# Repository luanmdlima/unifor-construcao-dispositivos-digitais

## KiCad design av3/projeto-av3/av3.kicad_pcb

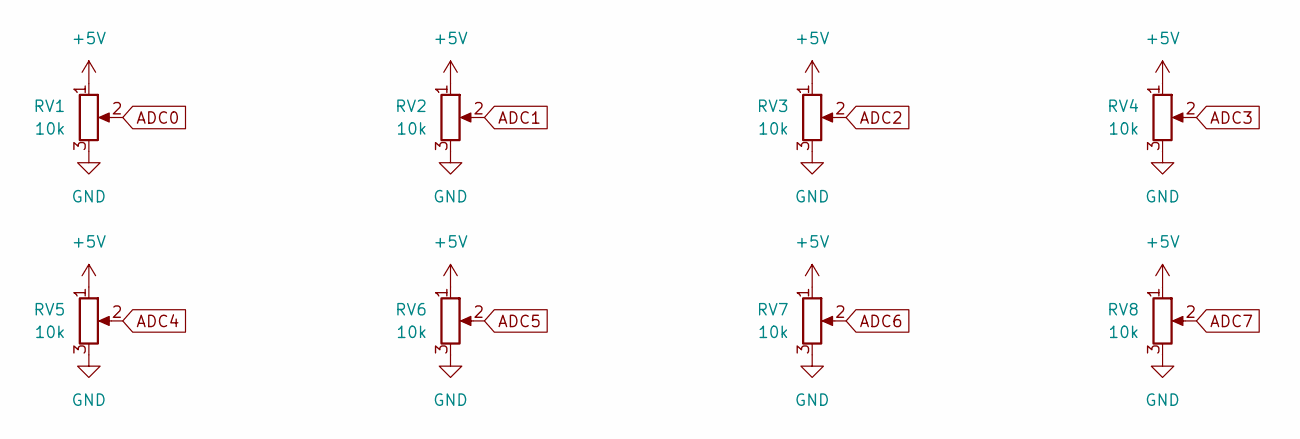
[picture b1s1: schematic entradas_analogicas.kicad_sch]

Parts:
RV1, RV2, RV3, RV4, RV5, RV6, RV7, RV8: 10k; Potentiometer_Bourns_3296W_Vertical

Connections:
+5V: RV1.1, RV2.1, RV3.1, RV4.1, RV5.1, RV6.1, RV7.1, RV8.1; also elsewhere on the board
ADC0: RV1.2; also elsewhere on the board
ADC1: RV2.2; also elsewhere on the board
ADC2: RV3.2; also elsewhere on the board
ADC3: RV4.2; also elsewhere on the board
ADC4: RV5.2; also elsewhere on the board
ADC5: RV6.2; also elsewhere on the board
ADC6: RV7.2; also elsewhere on the board
ADC7: RV8.2; also elsewhere on the board
GND: RV1.3, RV2.3, RV3.3, RV4.3, RV5.3, RV6.3, RV7.3, RV8.3; also elsewhere on the board

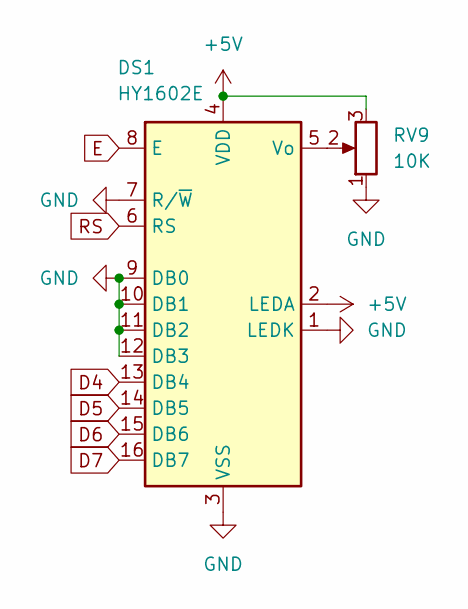
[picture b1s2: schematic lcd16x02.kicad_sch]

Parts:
DS1: HY1602E
RV9: 10K; Potentiometer_Bourns_3296W_Vertical

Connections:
+5V: DS1.2 (LEDA), DS1.4 (VDD), RV9.3; also elsewhere on the board
D4: DS1.13 (DB4); also elsewhere on the board
D5: DS1.14 (DB5); also elsewhere on the board
D6: DS1.15 (DB6); also elsewhere on the board
D7: DS1.16 (DB7); also elsewhere on the board
E: DS1.8 (E); also elsewhere on the board
GND: DS1.1 (LEDK), DS1.3 (VSS), DS1.7 (R/~W), DS1.9 (DB0), DS1.10 (DB1), DS1.11 (DB2), DS1.12 (DB3), RV9.1; also elsewhere on the board
unnamed: DS1.5 (Vo), RV9.2
RS: DS1.6 (RS); also elsewhere on the board

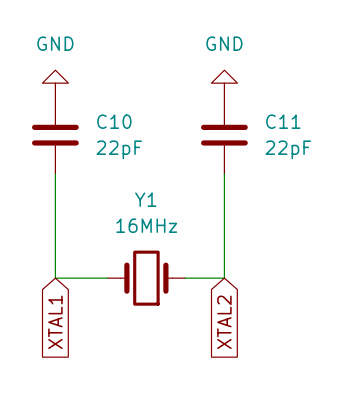
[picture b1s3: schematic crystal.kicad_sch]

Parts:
C10, C11: 22pF; C_1206_3216Metric
Y1: 16MHz; Crystal_SMD_HC49-SD

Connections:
GND: C10.2, C11.2; also elsewhere on the board
XTAL1: C10.1, Y1.2; also elsewhere on the board
XTAL2: C11.1, Y1.1; also elsewhere on the board

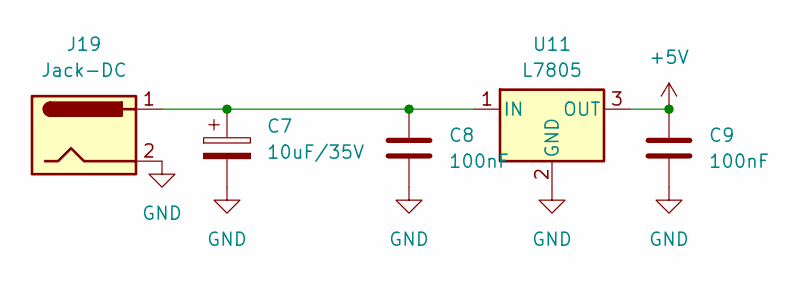
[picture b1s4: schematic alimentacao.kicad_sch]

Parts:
C7: 10uF/35V; CP_Elec_5x5.7
C8, C9: 100nF; C_1206_3216Metric
J19: Jack-DC; BarrelJack_Horizontal
U11: L7805; TO-220-3_Horizontal_TabDown

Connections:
+5V: C9.1, U11.3 (OUT); also elsewhere on the board
GND: C7.2, C8.2, C9.2, J19.2, U11.2 (GND); also elsewhere on the board
unnamed: C7.1, C8.1, J19.1, U11.1 (IN)

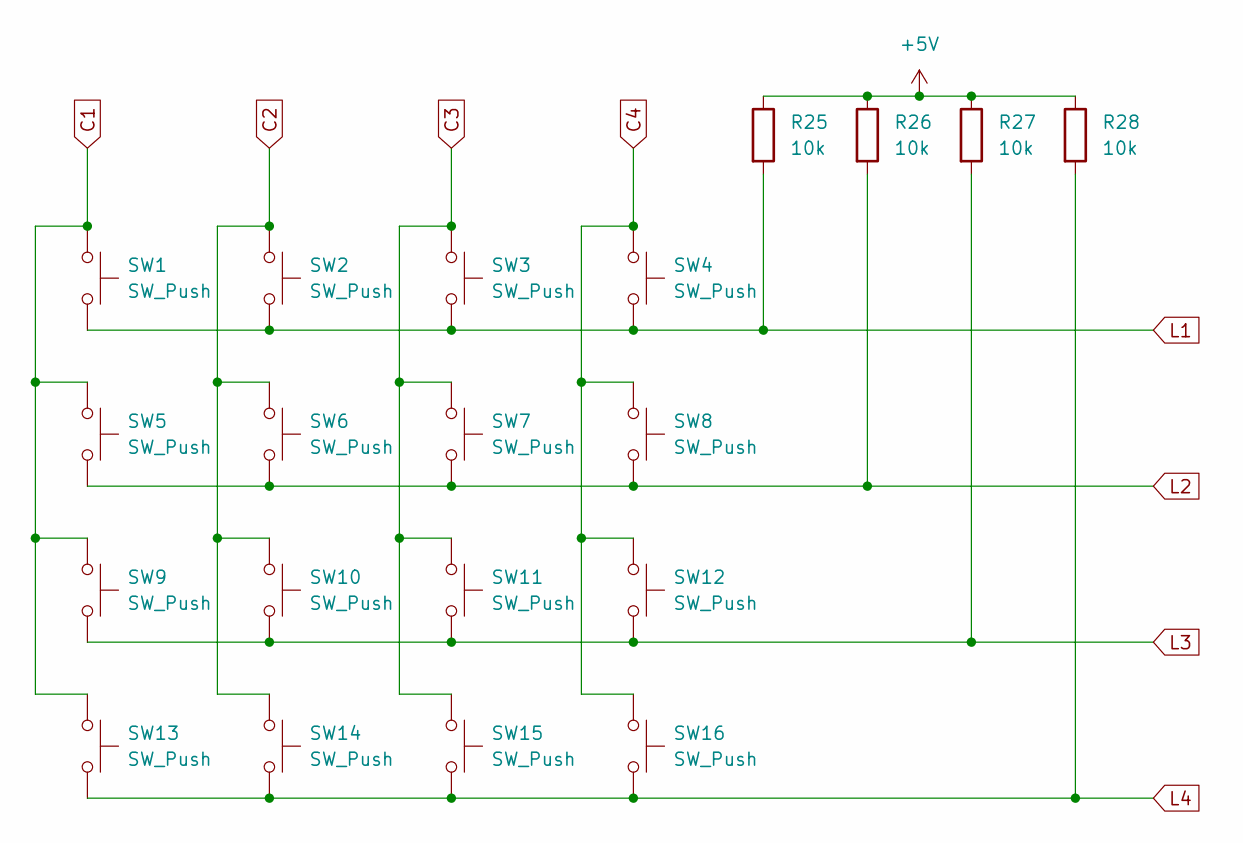
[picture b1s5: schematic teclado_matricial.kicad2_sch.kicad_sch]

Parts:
R25, R26, R27, R28: 10k; R_1206_3216Metric_Pad1.30x1.75mm_HandSolder
SW1, SW2, SW3, SW4, SW5, SW6, SW7, SW8, SW9, SW10, SW11, SW12, SW13, SW14, SW15, SW16: SW_Push; SW_PUSH_6mm_H4.3mm

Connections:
+5V: R25.1, R26.1, R27.1, R28.1; also elsewhere on the board
C1: SW1.1, SW5.1, SW9.1, SW13.1; also elsewhere on the board
C2: SW2.1, SW6.1, SW10.1, SW14.1; also elsewhere on the board
C3: SW3.1, SW7.1, SW11.1, SW15.1; also elsewhere on the board
C4: SW4.1, SW8.1, SW12.1, SW16.1; also elsewhere on the board
L1: R25.2, SW1.2, SW2.2, SW3.2, SW4.2; also elsewhere on the board
L2: R26.2, SW5.2, SW6.2, SW7.2, SW8.2; also elsewhere on the board
L3: R27.2, SW9.2, SW10.2, SW11.2, SW12.2; also elsewhere on the board
L4: R28.2, SW13.2, SW14.2, SW15.2, SW16.2; also elsewhere on the board

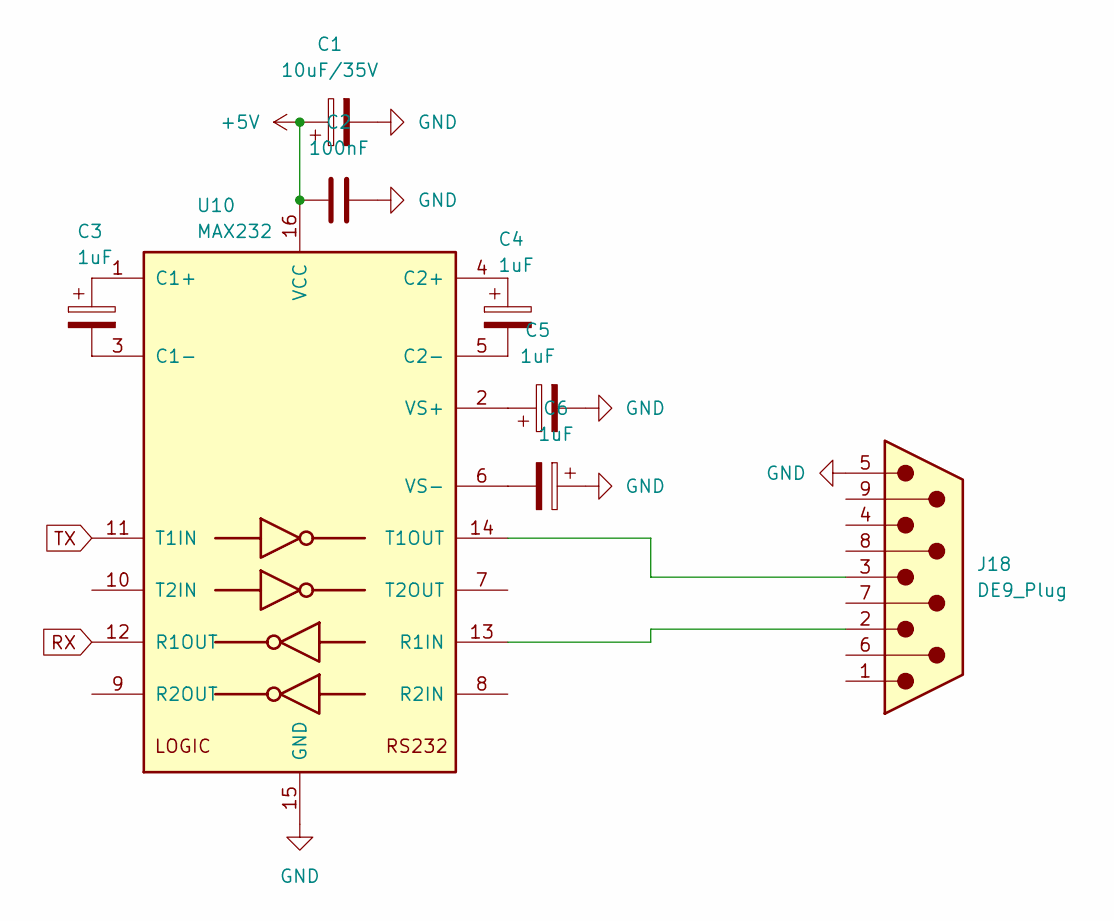
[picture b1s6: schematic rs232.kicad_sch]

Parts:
C1: 10uF/35V; CP_Elec_5x5.7
C2: 100nF; C_1206_3216Metric
C3, C4, C5, C6: 1uF; CP_Elec_3x5.3
J18: DE9_Plug; DSUB-9_Female_Horizontal_P2.77x2.84mm_EdgePinOffset4.94mm_H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
U10: MAX232; SOIC-16_4.55x10.3mm_P1.27mm

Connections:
+5V: C1.1, C2.1, U10.16 (VCC); also elsewhere on the board
GND: C1.2, C2.2, C5.2, C6.1, J18.5, U10.15 (GND); also elsewhere on the board
unnamed: C3.1, U10.1 (C1+)
unnamed: C3.2, U10.3 (C1-)
unnamed: C4.1, U10.4 (C2+)
unnamed: C4.2, U10.5 (C2-)
unnamed: J18.2, U10.13 (R1IN)
unnamed: J18.3, U10.14 (T1OUT)
unnamed: C5.1, U10.2 (VS+)
unnamed: C6.2, U10.6 (VS-)
RX: U10.12 (R1OUT); also elsewhere on the board
TX: U10.11 (T1IN); also elsewhere on the board

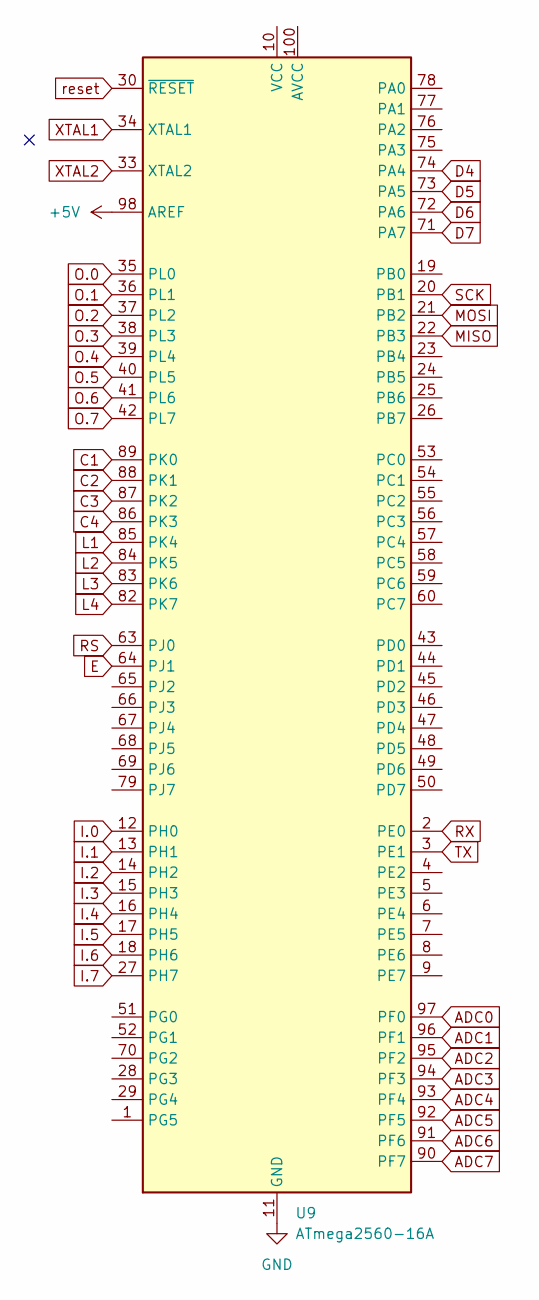
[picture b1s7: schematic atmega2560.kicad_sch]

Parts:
U9: ATmega2560-16A; TQFP-100_14x14mm_P0.5mm

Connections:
+5V: U9.98 (AREF); also elsewhere on the board
ADC0: U9.97 (PF0); also elsewhere on the board
ADC1: U9.96 (PF1); also elsewhere on the board
ADC2: U9.95 (PF2); also elsewhere on the board
ADC3: U9.94 (PF3); also elsewhere on the board
ADC4: U9.93 (PF4); also elsewhere on the board
ADC5: U9.92 (PF5); also elsewhere on the board
ADC6: U9.91 (PF6); also elsewhere on the board
ADC7: U9.90 (PF7); also elsewhere on the board
C1: U9.89 (PK0); also elsewhere on the board
C2: U9.88 (PK1); also elsewhere on the board
C3: U9.87 (PK2); also elsewhere on the board
C4: U9.86 (PK3); also elsewhere on the board
D4: U9.74 (PA4); also elsewhere on the board
D5: U9.73 (PA5); also elsewhere on the board
D6: U9.72 (PA6); also elsewhere on the board
D7: U9.71 (PA7); also elsewhere on the board
E: U9.64 (PJ1); also elsewhere on the board
GND: U9.11 (GND), U9.32 (GND), U9.62 (GND), U9.81 (GND), U9.99 (GND); also elsewhere on the board
I.0: U9.12 (PH0); also elsewhere on the board
I.1: U9.13 (PH1); also elsewhere on the board
I.2: U9.14 (PH2); also elsewhere on the board
I.3: U9.15 (PH3); also elsewhere on the board
I.4: U9.16 (PH4); also elsewhere on the board
I.5: U9.17 (PH5); also elsewhere on the board
I.6: U9.18 (PH6); also elsewhere on the board
I.7: U9.27 (PH7); also elsewhere on the board
L1: U9.85 (PK4); also elsewhere on the board
L2: U9.84 (PK5); also elsewhere on the board
L3: U9.83 (PK6); also elsewhere on the board
L4: U9.82 (PK7); also elsewhere on the board
MISO: U9.22 (PB3); also elsewhere on the board
MOSI: U9.21 (PB2); also elsewhere on the board
unnamed: U9.10 (VCC), U9.31 (VCC), U9.61 (VCC), U9.80 (VCC)
O.0: U9.35 (PL0); also elsewhere on the board
O.1: U9.36 (PL1); also elsewhere on the board
O.2: U9.37 (PL2); also elsewhere on the board
O.3: U9.38 (PL3); also elsewhere on the board
O.4: U9.39 (PL4); also elsewhere on the board
O.5: U9.40 (PL5); also elsewhere on the board
O.6: U9.41 (PL6); also elsewhere on the board
O.7: U9.42 (PL7); also elsewhere on the board
RS: U9.63 (PJ0); also elsewhere on the board
RX: U9.2 (PE0); also elsewhere on the board
SCK: U9.20 (PB1); also elsewhere on the board
TX: U9.3 (PE1); also elsewhere on the board
XTAL1: U9.34 (XTAL1); also elsewhere on the board
XTAL2: U9.33 (XTAL2); also elsewhere on the board
reset: U9.30 (~RESET); also elsewhere on the board

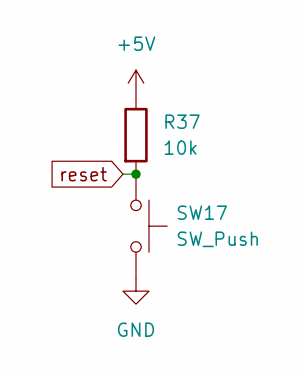
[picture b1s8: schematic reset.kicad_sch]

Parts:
R37: 10k; R_1206_3216Metric_Pad1.30x1.75mm_HandSolder
SW17: SW_Push; SW_PUSH_6mm_H4.3mm

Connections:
+5V: R37.1; also elsewhere on the board
GND: SW17.2; also elsewhere on the board
reset: R37.2, SW17.1; also elsewhere on the board

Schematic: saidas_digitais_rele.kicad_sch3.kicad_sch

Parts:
D17, D18, D19, D20, D21, D22, D23, D24: 1N4148; D_DO-35_SOD27_P7.62mm_Horizontal
J9, J10, J11, J12, J13, J14, J15, J16: Conn_01x03; TerminalBlock_Phoenix_MKDS-1,5-3-5.08_1x03_P5.08mm_Horizont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
K1, K2, K3, K4, K5, K6, K7, K8: SANYOU_SRD_Form_C; Relay_SPDT_SANYOU_SRD_Series_Form_C
Q1, Q2, Q3, Q4, Q5, Q6, Q7, Q8: BC548; TO-92_Inline
R29, R30, R31, R32, R33, R34, R35, R36: 1k; R_Axial_DIN0204_L3.6mm_D1.6mm_P5.08mm_Horizontal

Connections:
+5V: D17.1 (K), D18.1 (K), D19.1 (K), D20.1 (K), D21.1 (K), D22.1 (K), D23.1 (K), D24.1 (K), K1.2, K2.2, K3.2, K4.2, K5.2, K6.2, K7.2, K8.2; also elsewhere on the board
GND: Q1.3 (E), Q2.3 (E), Q3.3 (E), Q4.3 (E), Q5.3 (E), Q6.3 (E), Q7.3 (E), Q8.3 (E); also elsewhere on the board
unnamed: D17.2 (A), K1.5, Q1.1 (C)
unnamed: D18.2 (A), K2.5, Q2.1 (C)
unnamed: D19.2 (A), K3.5, Q3.1 (C)
unnamed: D20.2 (A), K4.5, Q4.1 (C)
unnamed: D21.2 (A), K5.5, Q5.1 (C)
unnamed: D22.2 (A), K6.5, Q6.1 (C)
unnamed: D23.2 (A), K7.5, Q7.1 (C)
unnamed: D24.2 (A), K8.5, Q8.1 (C)
unnamed: J9.1, K1.3
unnamed: J9.2, K1.1
unnamed: J9.3, K1.4
unnamed: J10.1, K2.3
unnamed: J10.2, K2.1
unnamed: J10.3, K2.4
unnamed: J11.1, K3.3
unnamed: J11.2, K3.1
unnamed: J11.3, K3.4
unnamed: J12.1, K4.3
unnamed: J12.2, K4.1
unnamed: J12.3, K4.4
unnamed: J13.1, K5.3
unnamed: J13.2, K5.1
unnamed: J13.3, K5.4
unnamed: J14.1, K6.3
unnamed: J14.2, K6.1
unnamed: J14.3, K6.4
unnamed: J15.1, K7.3
unnamed: J15.2, K7.1
unnamed: J15.3, K7.4
unnamed: J16.1, K8.3
unnamed: J16.2, K8.1
unnamed: J16.3, K8.4
unnamed: Q1.2 (B), R29.2
unnamed: Q2.2 (B), R30.2
unnamed: Q3.2 (B), R31.2
unnamed: Q4.2 (B), R32.2
unnamed: Q5.2 (B), R33.2
unnamed: Q6.2 (B), R34.2
unnamed: Q7.2 (B), R35.2
unnamed: Q8.2 (B), R36.2
O.0: R29.1; also elsewhere on the board
O.1: R30.1; also elsewhere on the board
O.2: R31.1; also elsewhere on the board
O.3: R32.1; also elsewhere on the board
O.4: R33.1; also elsewhere on the board
O.5: R34.1; also elsewhere on the board
O.6: R35.1; also elsewhere on the board
O.7: R36.1; also elsewhere on the board

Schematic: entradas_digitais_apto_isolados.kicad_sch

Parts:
D1, D2, D3, D4, D9, D10, D12, D13: 1N4148; D_DO-35_SOD27_P7.62mm_Horizontal
D5, D6, D7, D8, D11, D14, D15, D16: LED; LED_1206_3216Metric
J1, J2, J3, J4, J5, J6, J7, J8: Conn_01x02; TerminalBlock_Phoenix_MKDS-1,5-2_1x02_P5.00mm_Horizontal
R1, R2, R3, R4, R5, R6, R7, R8, R13, R14, R15, R17, R18, R19, R20, R22: 10k; R_1206_3216Metric_Pad1.30x1.75mm_HandSolder
R9, R10, R11, R12, R16, R21, R23, R24: 1k; R_1206_3216Metric_Pad1.30x1.75mm_HandSolder
U1, U2, U3, U4, U5, U6, U7, U8: 4N25; DIP-6_W7.62mm_SMDSocket_SmallPads

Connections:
+5V: D1.1 (K), D2.1 (K), D3.1 (K), D4.1 (K), D9.1 (K), D10.1 (K), D12.1 (K), D13.1 (K), R5.2, R6.2, R7.2, R8.2, R14.2, R18.2, R20.2, R22.2; also elsewhere on the board
GND: U1.4, U2.4, U3.4, U4.4, U5.4, U6.4, U7.4, U8.4; also elsewhere on the board
I.0: R5.1, U1.5; also elsewhere on the board
I.1: R6.1, U2.5; also elsewhere on the board
I.2: R7.1, U3.5; also elsewhere on the board
I.3: R8.1, U4.5; also elsewhere on the board
I.4: R14.1, U5.5; also elsewhere on the board
I.5: R18.1, U6.5; also elsewhere on the board
I.6: R20.1, U7.5; also elsewhere on the board
I.7: R22.1, U8.5; also elsewhere on the board
unnamed: D1.2 (A), U1.6
unnamed: D2.2 (A), U2.6
unnamed: D3.2 (A), U3.6
unnamed: D4.2 (A), U4.6
unnamed: D5.2 (A), R9.2
unnamed: D5.1 (K), J1.2, U1.2
unnamed: D6.2 (A), R10.2
unnamed: D6.1 (K), J2.2, U2.2
unnamed: D7.2 (A), R11.2
unnamed: D7.1 (K), J3.2, U3.2
unnamed: D8.2 (A), R12.2
unnamed: D8.1 (K), J4.2, U4.2
unnamed: D9.2 (A), U5.6
unnamed: D10.2 (A), U6.6
unnamed: D11.2 (A), R16.2
unnamed: D11.1 (K), J5.2, U5.2
unnamed: D12.2 (A), U7.6
unnamed: D13.2 (A), U8.6
unnamed: D14.2 (A), R21.2
unnamed: D14.1 (K), J6.2, U6.2
unnamed: D15.2 (A), R23.2
unnamed: D15.1 (K), J7.2, U7.2
unnamed: D16.2 (A), R24.2
unnamed: D16.1 (K), J8.2, U8.2
unnamed: J1.1, R1.1, R9.1
unnamed: J2.1, R2.1, R10.1
unnamed: J3.1, R3.1, R11.1
unnamed: J4.1, R4.1, R12.1
unnamed: J5.1, R13.1, R16.1
unnamed: J6.1, R15.1, R21.1
unnamed: J7.1, R17.1, R23.1
unnamed: J8.1, R19.1, R24.1
unnamed: R1.2, U1.1
unnamed: R2.2, U2.1
unnamed: R3.2, U3.1
unnamed: R4.2, U4.1
unnamed: R13.2, U5.1
unnamed: R15.2, U6.1
unnamed: R17.2, U7.1
unnamed: R19.2, U8.1

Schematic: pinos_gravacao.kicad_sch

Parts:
J17: Conn_02x03_Odd_Even; PinHeader_2x03_P2.54mm_Vertical_SMD

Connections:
+5V: J17.2; also elsewhere on the board
GND: J17.6; also elsewhere on the board
MISO: J17.1; also elsewhere on the board
MOSI: J17.4; also elsewhere on the board
SCK: J17.3; also elsewhere on the board
reset: J17.5; also elsewhere on the board

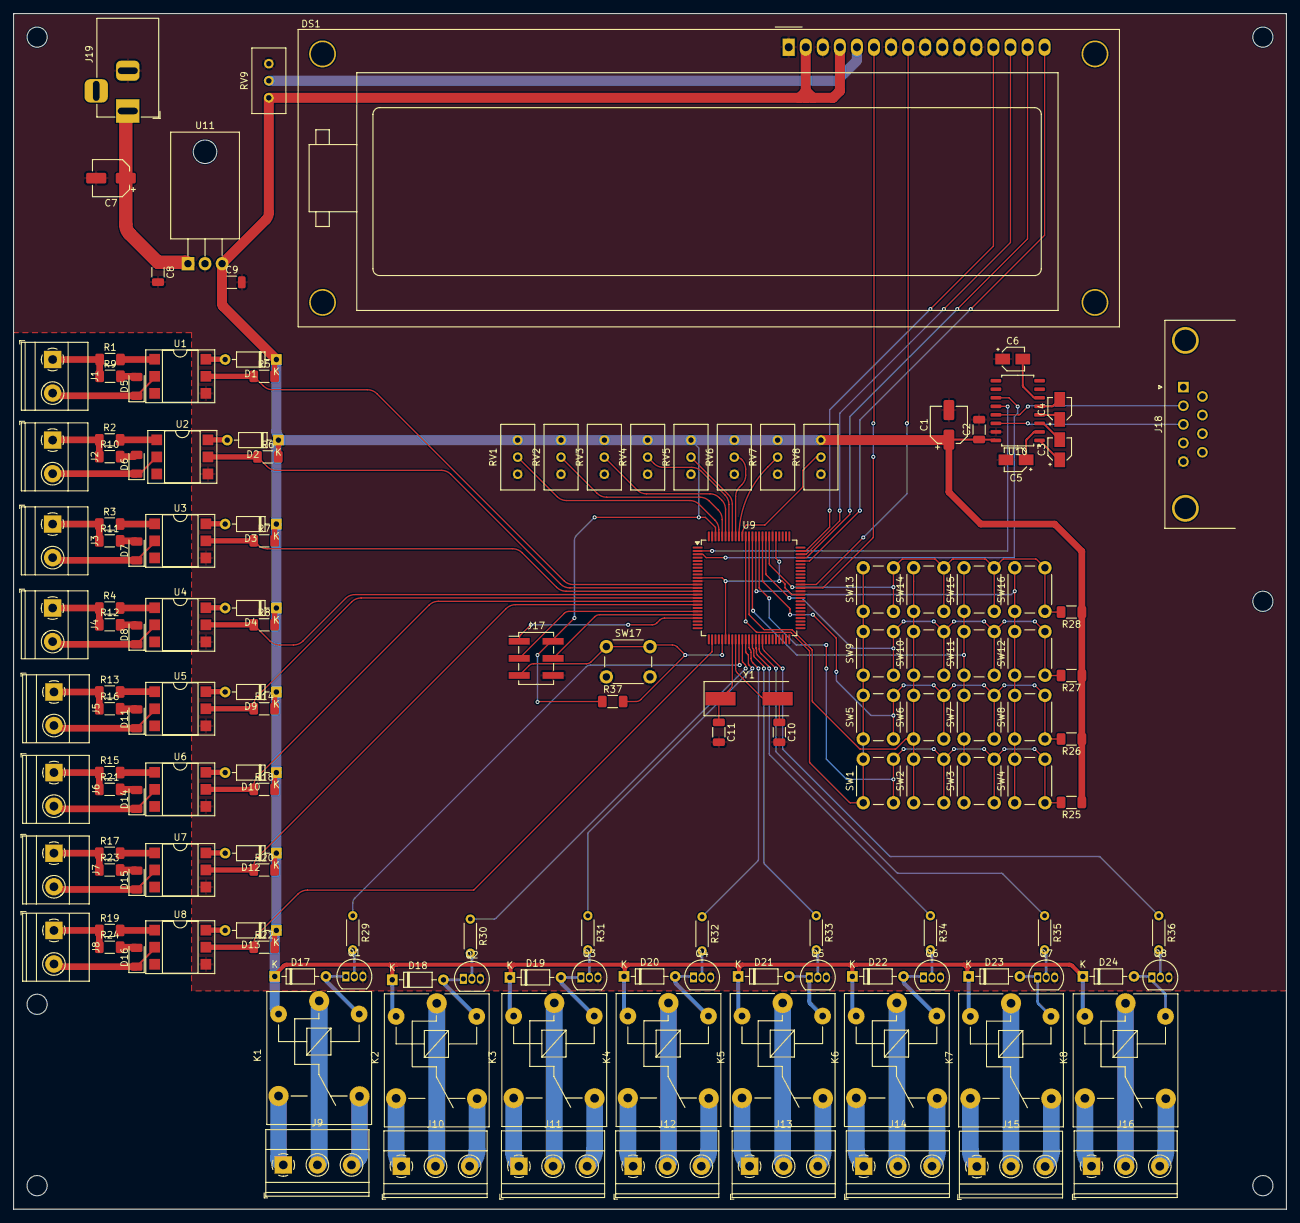
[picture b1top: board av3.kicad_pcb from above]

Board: 2 copper layers, 189.5 x 178.0 mm, 146 parts (0 on the bottom side), 139 nets.

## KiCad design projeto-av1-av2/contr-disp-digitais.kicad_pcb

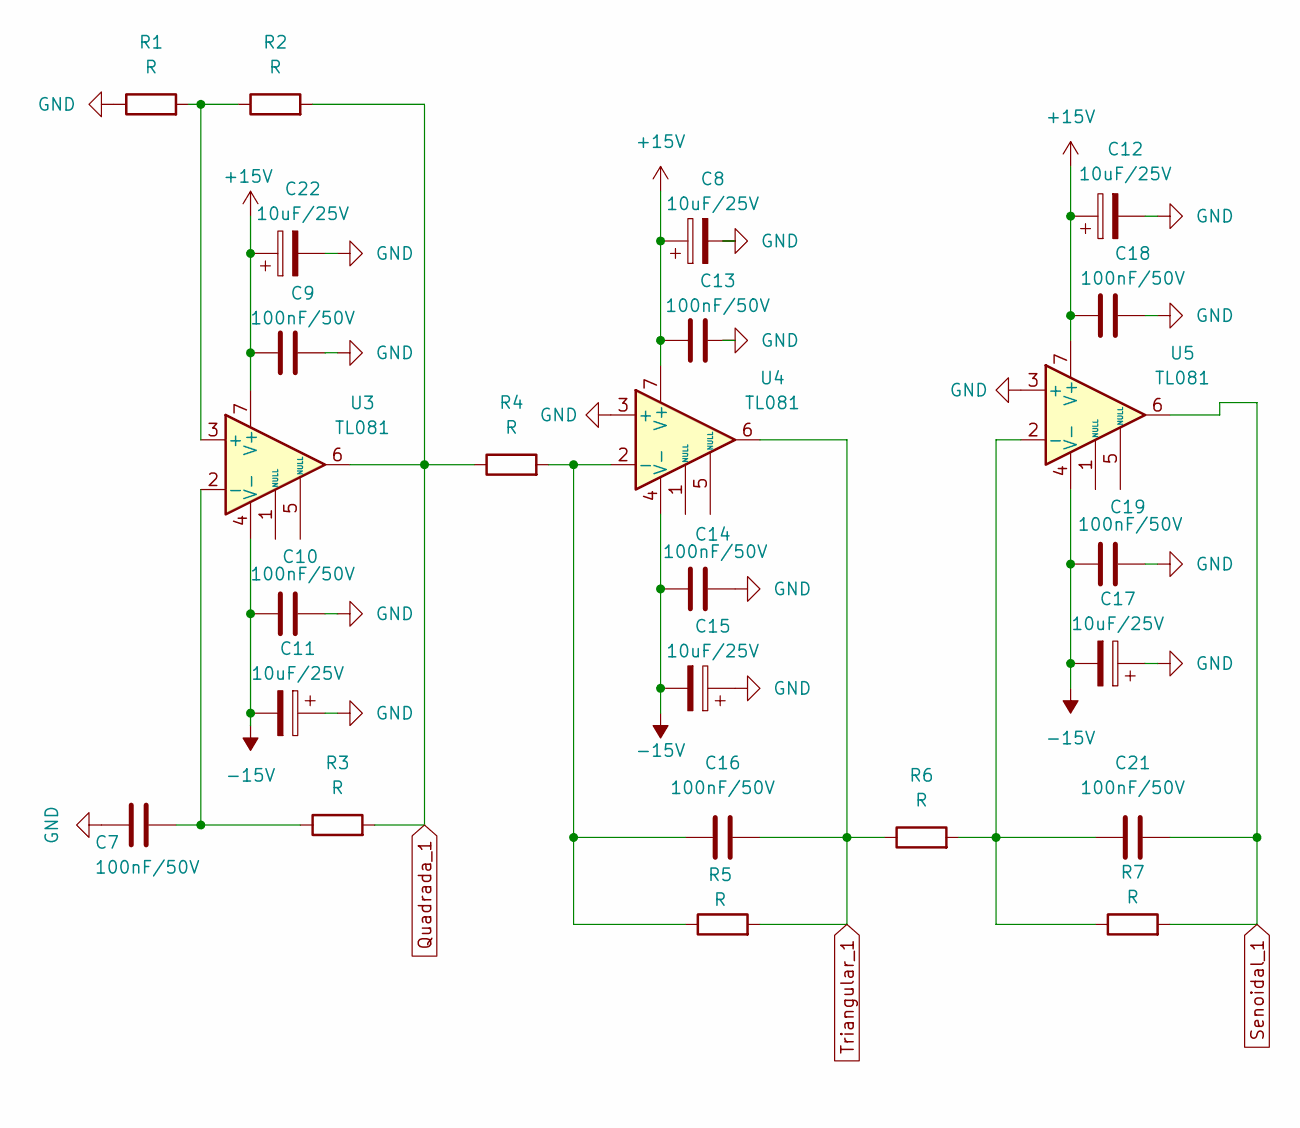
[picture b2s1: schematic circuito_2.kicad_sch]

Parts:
C7, C9, C10, C13, C14, C16, C18, C19, C21: 100nF/50V; C_0805_2012Metric
C8, C11, C12, C15, C17, C22: 10uF/25V; CP_Elec_4x5.8
R1, R2, R3, R4, R5, R6, R7: R; R_0805_2012Metric
U3, U4, U5: TL081; DIP-8_W7.62mm_LongPads

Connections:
+15V: C8.1, C9.1, C12.1, C13.1, C18.1, C22.1, U3.7 (V+), U4.7 (V+), U5.7 (V+); also elsewhere on the board
-15V: C10.1, C11.2, C14.1, C15.2, C17.2, C19.1, U3.4 (V-), U4.4 (V-), U5.4 (V-); also elsewhere on the board
GND: C7.2, C8.2, C9.2, C10.2, C11.1, C12.2, C13.2, C14.2, C15.1, C17.1, C18.2, C19.2, C22.2, R1.1, U4.3 (+), U5.3 (+); also elsewhere on the board
unnamed: R1.2, R2.1, U3.3 (+)
unnamed: C7.1, R3.1, U3.2 (-)
unnamed: C16.1, R4.2, R5.1, U4.2 (-)
unnamed: C21.1, R6.2, R7.1, U5.2 (-)
Quadrada_1: R2.2, R3.2, R4.1, U3.6; also elsewhere on the board
Senoidal_1: C21.2, R7.2, U5.6; also elsewhere on the board
Triangular_1: C16.2, R5.2, R6.1, U4.6; also elsewhere on the board

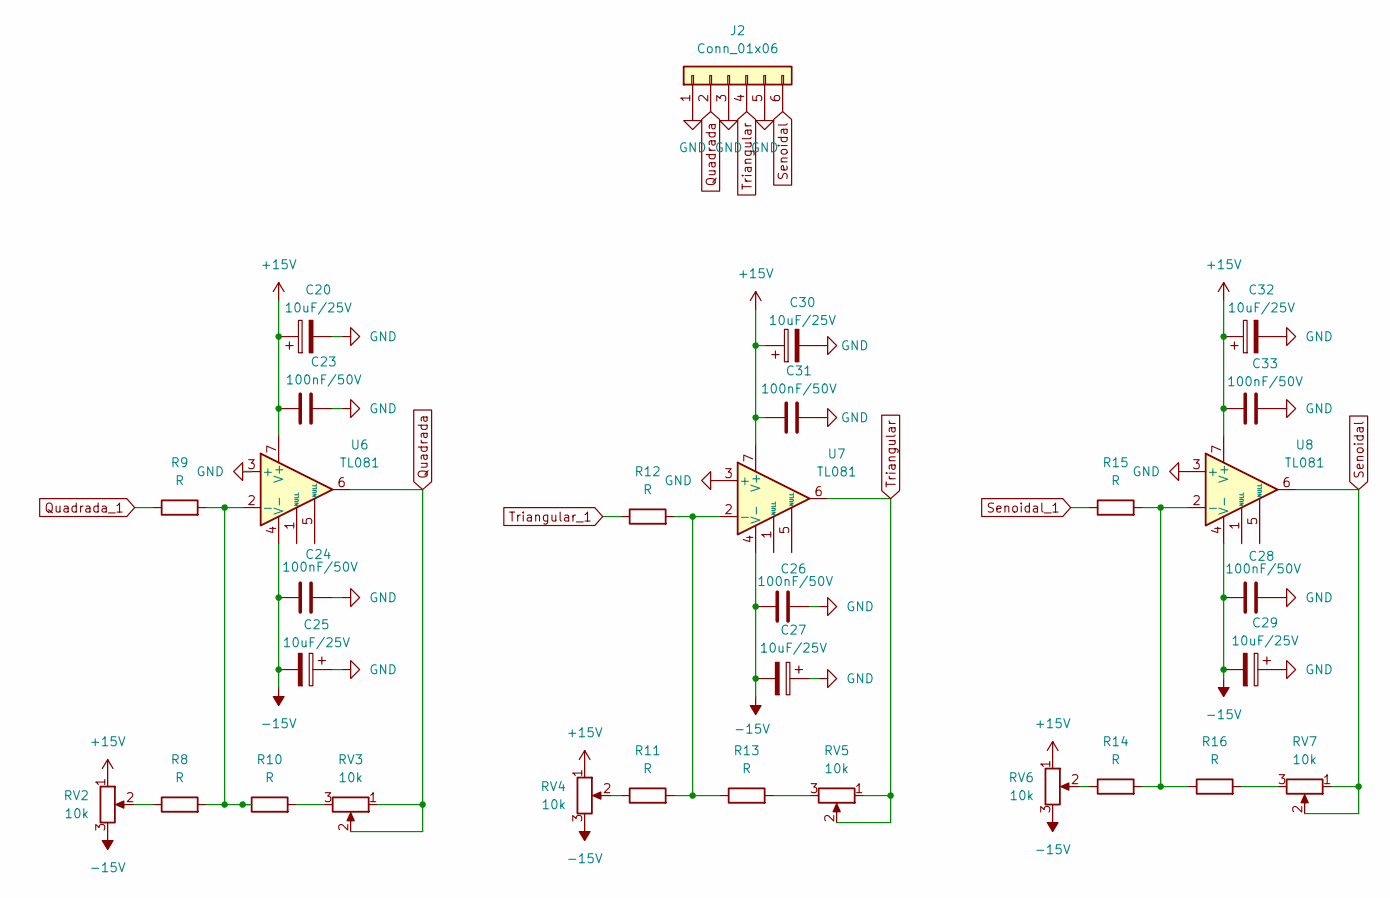
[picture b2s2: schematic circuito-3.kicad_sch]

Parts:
C20, C25, C27, C29, C30, C32: 10uF/25V; CP_Elec_4x5.8
C23, C24, C26, C28, C31, C33: 100nF/50V; C_0805_2012Metric
J2: Conn_01x06; PinHeader_1x06_P2.54mm_Vertical
R8, R9, R10, R11, R12, R13, R14, R15, R16: R; R_0805_2012Metric
RV2, RV3, RV4, RV5, RV6, RV7: 10k; Potentiometer_Bourns_3296W_Vertical
U6, U7, U8: TL081; DIP-8_W7.62mm_LongPads

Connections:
+15V: C20.1, C23.1, C30.1, C31.1, C32.1, C33.1, RV2.1, RV4.1, RV6.1, U6.7 (V+), U7.7 (V+), U8.7 (V+); also elsewhere on the board
-15V: C24.1, C25.2, C26.1, C27.2, C28.1, C29.2, RV2.3, RV4.3, RV6.3, U6.4 (V-), U7.4 (V-), U8.4 (V-); also elsewhere on the board
GND: C20.2, C23.2, C24.2, C25.1, C26.2, C27.1, C28.2, C29.1, C30.2, C31.2, C32.2, C33.2, J2.1, J2.3, J2.5, U6.3 (+), U7.3 (+), U8.3 (+); also elsewhere on the board
unnamed: R8.1, RV2.2
unnamed: R10.2, RV3.3
unnamed: R11.1, RV4.2
unnamed: R13.2, RV5.3
unnamed: R14.1, RV6.2
unnamed: R16.2, RV7.3
unnamed: R8.2, R9.2, R10.1, U6.2 (-)
unnamed: R11.2, R12.2, R13.1, U7.2 (-)
unnamed: R14.2, R15.2, R16.1, U8.2 (-)
Quadrada: J2.2, RV3.1, RV3.2, U6.6
Quadrada_1: R9.1; also elsewhere on the board
Senoidal: J2.6, RV7.1, RV7.2, U8.6
Senoidal_1: R15.1; also elsewhere on the board
Triangular: J2.4, RV5.1, RV5.2, U7.6
Triangular_1: R12.1; also elsewhere on the board

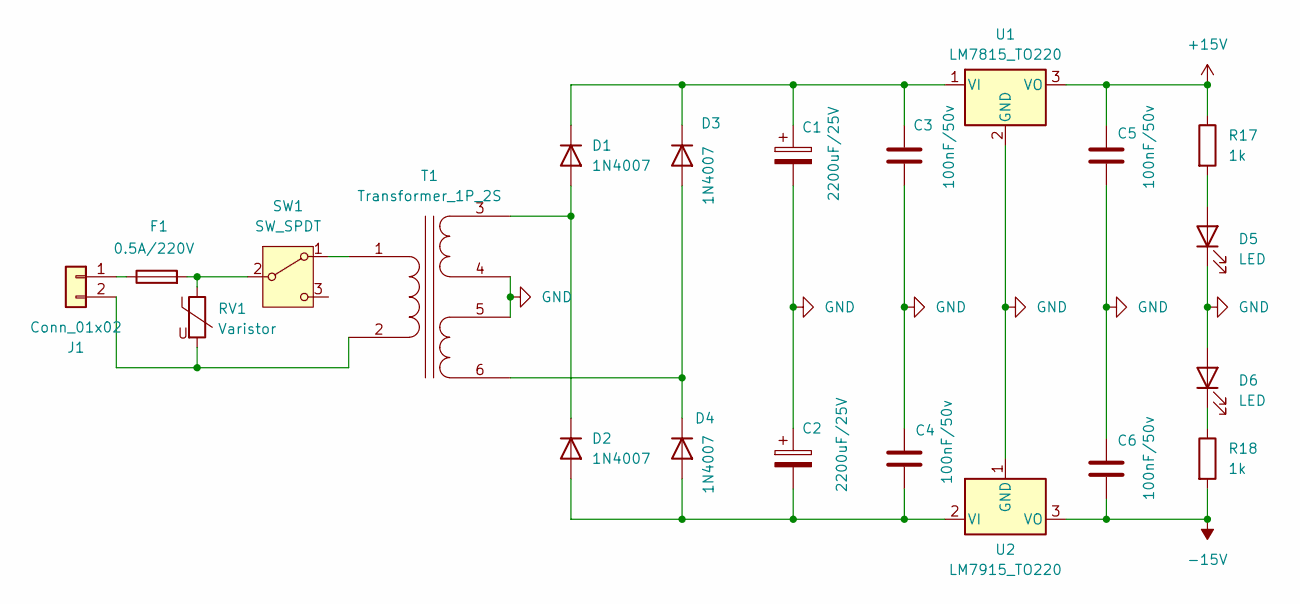
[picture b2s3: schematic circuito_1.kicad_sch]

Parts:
C1, C2: 2200uF/25V; CP_Radial_D10.0mm_P3.50mm
C3, C4, C5, C6: 100nF/50v; C_Disc_D3.4mm_W2.1mm_P2.50mm
D1, D2, D3, D4: 1N4007; D_DO-41_SOD81_P10.16mm_Horizontal
D5, D6: LED; LED_0805_2012Metric
F1: 0.5A/220V; Fuseholder_Clip-5x20mm_Keystone_3512P_Inline_P23.62x7.27mm_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
J1: Conn_01x02; TerminalBlock_Phoenix_MKDS-1,5-2-5.08_1x02_P5.08mm_Horizont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
R17, R18: 1k; R_0805_2012Metric
RV1: Varistor; RV_Disc_D12mm_W4.7mm_P7.5mm
SW1: SW_SPDT; SW_NKK_BB15AH
T1: Transformer_1P_2S; Transformer_CHK_EI48-8VA_2xSec
U1: LM7815_TO220; TO-220-3_Vertical
U2: LM7915_TO220; TO-220-3_Vertical

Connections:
+15V: C5.1, R17.1, U1.3 (VO); also elsewhere on the board
-15V: C6.2, R18.2, U2.3 (VO); also elsewhere on the board
GND: C1.2, C2.1, C3.2, C4.1, C5.2, C6.1, D5.1 (K), D6.2 (A), T1.4 (SB), T1.5 (SC), U1.2 (GND), U2.1 (GND); also elsewhere on the board
unnamed: D1.2 (A), D2.1 (K), T1.3 (SA)
unnamed: C1.1, C3.1, D1.1 (K), D3.1 (K), U1.1 (VI)
unnamed: C2.2, C4.2, D2.2 (A), D4.2 (A), U2.2 (VI)
unnamed: D3.2 (A), D4.1 (K), T1.6 (SD)
unnamed: D5.2 (A), R17.2
unnamed: D6.1 (K), R18.1
unnamed: F1.1, J1.1
unnamed: J1.2, RV1.2, T1.2 (AB)
unnamed: SW1.1 (A), T1.1 (AA)
unnamed: F1.2, RV1.1, SW1.2 (B)

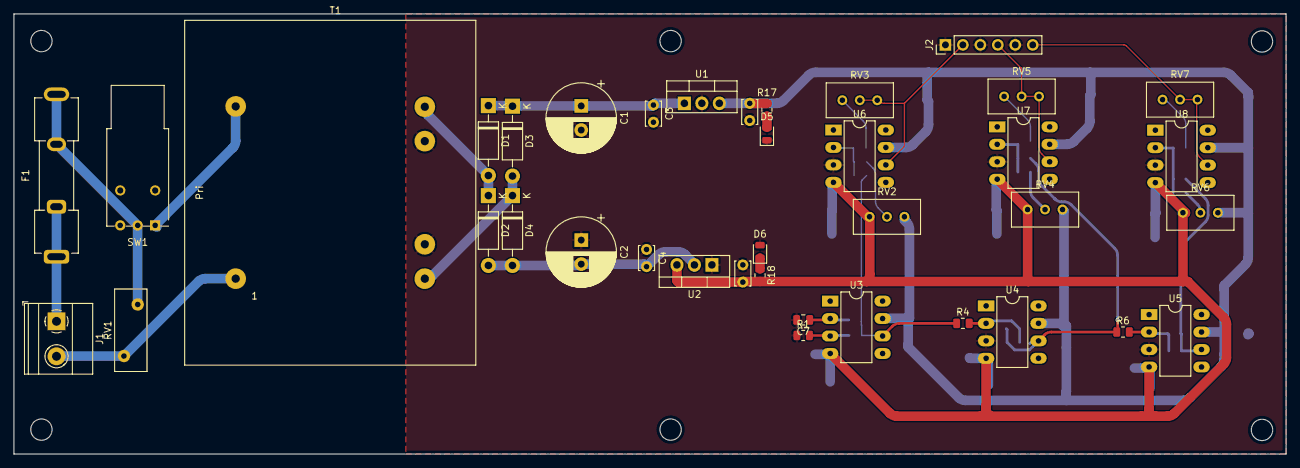
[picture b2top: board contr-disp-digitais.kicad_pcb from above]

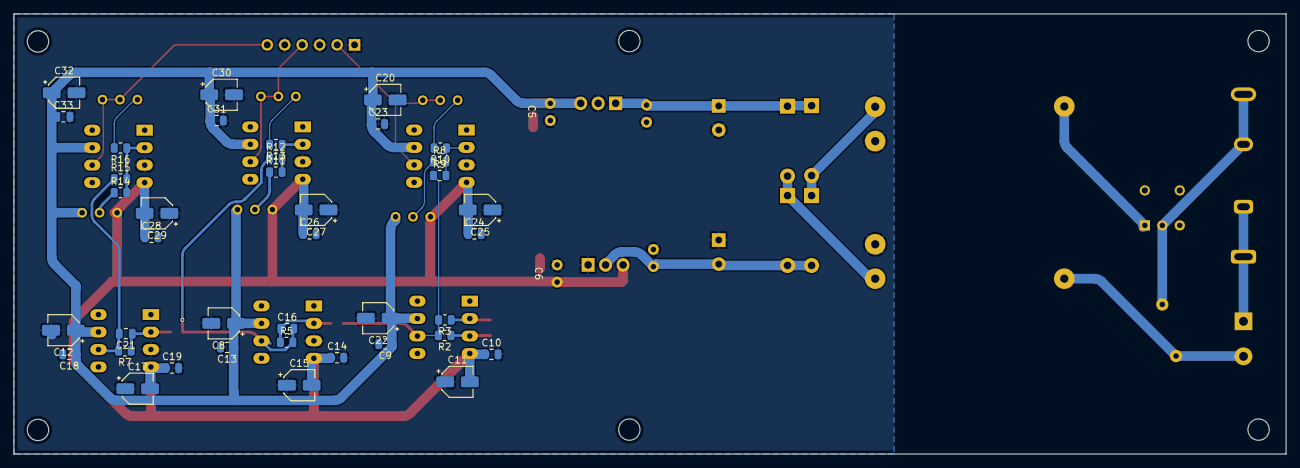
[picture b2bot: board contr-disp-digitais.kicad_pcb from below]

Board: 2 copper layers, 185.0 x 64.0 mm, 77 parts (39 on the bottom side), 32 nets.

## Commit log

2024-03-27 Commit inicial. Somente com o circuito 3.
2024-03-27 Circuito 2 adicionado
2024-04-04 Reorganização dos esquemáticos em pages.
2024-04-08 Footprints parcialmente adicionados.
2024-04-08 Relação de footprints finalizada.
2024-04-11 Alterações no schematic para bater com o que o professor mandoou no gropo. Pendente revisão.
2024-04-15 Revisão de schematics finalizado. Posicionamentos dos componentes do circuito 1 e 2 no PCB editor.
2024-04-15 Finalização de posicionamento de componentes no PCB, REVISÃO PENDENTE!!!
2024-04-17 Trilhas de alimentação finalizadas no PCB, alterações futuras possíveis e prováveis.
2024-04-18 Todas as trilhas finalizadas. Faltando para finalizar somente consertar 3 erros que remanescem, revisar e fazer melhorias possíveis até o dia da entrega.
2024-04-18 Erros tratados e furações de suporte incluídos. Remanesce somente a revisão geral para a entrega.
2024-04-30 Reestruturação do repo dividindo entre as etapas de avaliação.
2024-04-30 Ligação do cristal no atmega2560 e início do esquemático das saídas digitais com relé.
2024-05-22 Maioria dos esquemáticos finalizados.
2024-06-08 Esquemático finalizado, faltando somente o PCB.
2024-06-08 Referencias de componentes resetados; Progresso de 20% no PCB;
2024-06-14 Maioria das conexões do PBC feitas, e erros faltando corrigir.
2024-06-14 Montagem base finalizada.
